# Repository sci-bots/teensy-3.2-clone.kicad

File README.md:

# Teensy 3.2 reference board clone

Teensy 3.2 reference board recreated in KiCad. This is based on a conversion of the original [eagle project](https://github.com/thewknd/teensy-boards) by [thewknd](https://github.com/thewknd).

Shared basket at mouser: http://www.mouser.com/ProjectManager/ProjectDetail.aspx?AccessID=719df5721e

Pre-programmed Bootloader Chip for DIY Teensy LC & 3.2 Projects: http://pjrc.com/store/ic_mkl02.html (IC_MKL04Z32_TQFP32)

Shared project on osh park: https://www.oshpark.com/shared_projects/h2HB6bQQ

### What is different from the "original" Teensy 3.2 DIY Reference Board

PJRC Teensy 3.2 DIY Reference Board https://www.oshpark.com/shared_projects/d3J03Zeb

- the silkscreen is a bit messed up  
  
- the actuator from the tactile switch is shorter (ALPS SKHHPKA010)

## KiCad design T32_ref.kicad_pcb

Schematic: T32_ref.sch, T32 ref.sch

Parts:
C1, C4, C5, C7, C8, C9, C12: 0.1uF; C_0603; Mfg_Part_No GRM155R71A104KA01D
C2, C3, C6: 2.2uF; C_0805; Mfg_Part_No TMK212B7225KG-TR
C10, C11: 22pF; C_0603; Mfg_Part_No VJ0603A220JXACW1BC
G1: 16MHz; HC49US; Mfg_Part_No ABL-16.000MHz-B1U
G2: 32.768kHz; TC26H; Mfg_Part_No CFS206-32.768KDZF-UB
K1: MK20DX256VLH7; LQFP64-05; Mfg_Part_No MK20DX256VLH7
K2: MKL04Z32VLC4; LQFP32-08
P1: LED_0805; Mfg_Part_No SML-211DTT86
R1: FUSE; R_0805; Mfg_Part_No 0ZCK0050FF2E
R2, R4: R_0603; Mfg_Part_No BLM18AG601SN1D
R3, R8: 470R; R_0603; Mfg_Part_No CRCW0603470RFKEA
R5, R6: 33R; R_0603; Mfg_Part_No ERJ-PA3F33R0V
R7: SOT-23; Mfg_Part_No BAT54C,215
S1: ALPS_SKHH; Mfg_Part_No SKHHPKA010
SJ1: SOLDERJUMPER
SX1, SX2, SX3, SX4, SX5, SX6, SX7, SX8, SX9, SX10, SX11, SX12, SX13, SX14, SX15, SX16, SX17, SX18, SX19, SX20, SX21, SX22, SX23, SX24, SX25, SX26, SX27, SX28, SX29, SX30, SX31, SX32, SX33, SX34, SX35, SX36, SX37, SX38, SX39, SX40, SX41, SX42, SX43, SX44, SX45, SX46, SX47, SX48, SX49, SX50, SX51, SX52, SX53, SX54, SX55, SX56, SX57, SX58, SX59, SX60: PIN; PTH_39MIL
T1: MCP1825S; SOT-223; Mfg_Part_No MCP1825S-3302E/DB
X1: MINI-USB; MOLEX_SD-67503-010; Mfg_Part_No 67503-1020

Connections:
/N$1: K2.7 (PTA3), SX59.1
/N$2: K1.22 (PTA0), K2.16 (PTB0), SX58.1
/N$3: K1.24 (PTA2), K2.17 (PTB1)
/N$5: C10.1, G1.1, K1.32 (PTA18)
/N$6: C11.1, G1.2, K1.33 (PTA19)
/N$7: G2.2 (1), K1.19 (XTAL32)
/N$8: G2.1 (2), K1.20 (EXTAL32)
/N$9: K2.18 (PTB2), S1.1, S1.2 (1), SX40.1
/N$10: K1.5 (USB0_DP), R6.2
/N$11: C8.1, K1.17 (VREF_OUT)
/N$12: K1.34 (RESET_B), K2.8 (PTA4), K2.25 (PTB5), SX38.1, SX56.1
/N$13: C7.1, K1.14 (VREFH), R3.2, SX16.1
/N$14: K1.6 (USB0_DM), R5.2
/N$15: C6.1, K1.13 (VDDA), R2.1, R3.1
/N$16: R6.1, X1.3
/N$17: R5.1, X1.2
/N$18: C3.1, R1.1, X1.1
/N$19: K1.23 (PTA1), K2.10 (PTA6), X1.4
/N$21: K1.45 (PTC2), SX5.1
/N$22: K1.44 (PTC1), SX6.1
/N$23: K1.63 (PTD6), SX7.1
/N$24: K1.62 (PTD5), SX8.1
/N$25: K1.37 (PTB2), SX9.1
/N$26: K1.38 (PTB3), SX10.1
/N$27: K1.36 (PTB1), SX11.1
/N$28: K1.35 (PTB0), SX13.1
/N$29: K1.43 (PTC0), SX15.1
/N$30: K1.58 (PTD1), SX17.1
/N$31: K1.50 (PTC5), P1.2, P1.+, SX18.1
/N$32: K1.52 (PTC7), SX19.1
/N$33: K1.51 (PTC6), SX20.1
/N$34: K1.49 (PTC4), SX21.1
/N$35: K1.46 (PTC3), SX22.1
/N$36: K1.60 (PTD3), SX23.1
/N$37: K1.59 (PTD2), SX24.1
/N$38: K1.61 (PTD4), SX25.1
/N$39: K1.64 (PTD7), SX26.1
/N$40: K1.29 (PTA13), SX27.1
/N$41: K1.28 (PTA12), SX28.1
/N$42: K1.57 (PTD0), SX29.1
/N$43: K1.40 (PTB17), SX30.1
/N$44: K1.39 (PTB16), SX31.1
/N$45: K1.12 (ADC0_DM3), SX33.1
/N$46: K1.26 (PTA4), SX35.1
/N$47: K1.41 (PTB18), SX36.1
/N$48: K1.1 (PTE0), SX37.1
/N$49: K1.56 (PTC11), SX39.1
/N$50: K1.55 (PTC10), SX41.1
/N$51: K1.53 (PTC8), SX43.1
/N$52: P1.1, P1.-, R8.2
/N$53: C6.2, C7.2, C8.2, K1.15 (VREFL), K1.16 (VSSA), R4.2, SX3.1
/N$54: K1.18 (DAC0), SX52.1
/N$55: K1.11 (ADC0_DP3), SX51.1
/N$57: K1.27 (PTA5), SX49.1
/N$58: K1.42 (PTB19), SX48.1
/N$59: K1.2 (PTE1), SX47.1
/N$60: K1.54 (PTC9), SX45.1
/N$61: C1.1, SJ1.2, SX2.1, T1.1 (IN)
/N$63: R7.2, SX46.1
/N$64: K1.10 (ADC0_DM0), SX12.1
/N$65: K1.9 (ADC0_DP0), SX14.1
/N$67: R1.2, SJ1.1, SX1.1
/N$68: C9.1, K1.21 (VBAT), R7.3
/N$69: C2.1, C4.1, C5.1, C12.1, K1.3 (VDD), K1.7 (VOUT33), K1.30 (VDD), K1.48 (VDD), K2.3 (VDD), K2.4 (VREFH), R2.2, R7.1, SX4.1, SX34.1, SX44.1, SX54.1, T1.3 (OUT)
/N$70: K1.25 (PTA3), K2.15 (PTA7), SX57.1
GND: C1.2, C2.2, C3.2, C4.2, C5.2, C9.2, C10.2, C11.2, C12.2, K1.4 (VSS), K1.31 (VSS), K1.47 (VSS), K2.5 (VREFL), K2.6 (VSS), R4.1, R8.1, S1.3, S1.4 (3), SX32.1, SX42.1, SX50.1, SX53.1, SX55.1, SX60.1, T1.2 (GND), T1.4, T1.PAD, X1.5, X1.P$1 (CASE), X1.P$2 (CASE), X1.P$3 (CASE), X1.P$4 (CASE), X1.P$5 (CASE), X1.P$6 (CASE)

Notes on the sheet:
VIN
AGND
3.3V
23 / A9
22 / A8
21 / A7
20 / A6
19 / A5
18 / A4
17 / A3
16 / A2
15 / A1
14 / A0
13 (LED)
GND
A13
A12
DAC / A14
VBAT
RESET
PROG
A11
A10
AREF
VUSB
SWD
SWC
EN'

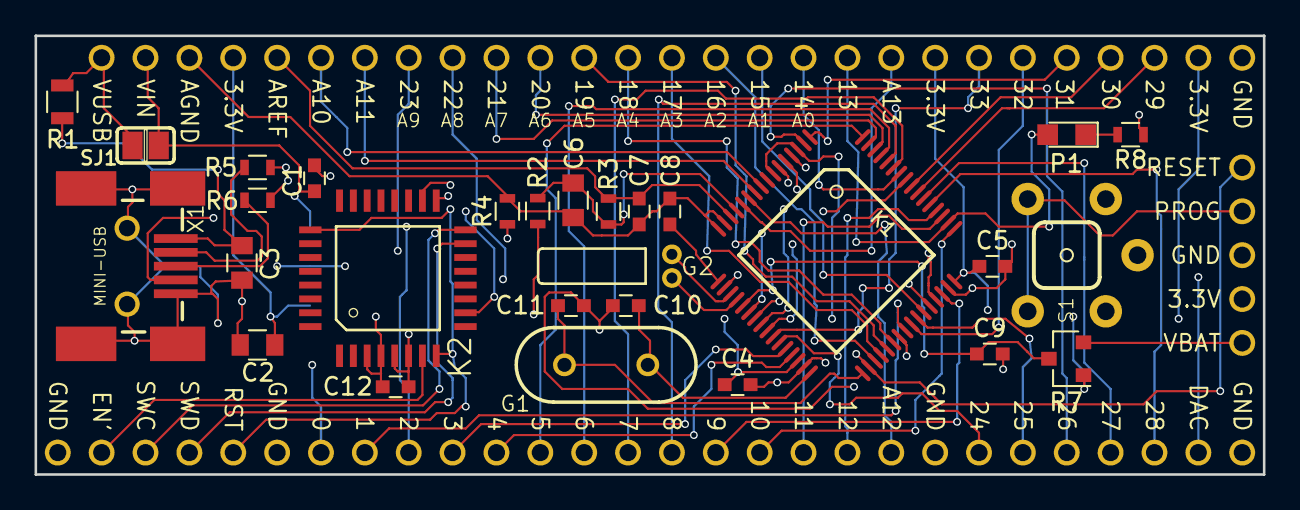
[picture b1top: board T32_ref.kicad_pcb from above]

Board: 4 copper layers, 71.1 x 25.4 mm, 89 parts (0 on the bottom side), 66 nets.

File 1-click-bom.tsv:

References,Qty,Description,Part Number,Digi-Key,Mouser,Newark
"C1, C4, C5, C7, C8, C9, C12",7,0.1uF,GRM155R71A104KA01D,490-6321-1-ND,GRM155R71A104KA01D,14T3278
"C2, C3, C6",3,2.2uF,TMK212B7225KG-TR,587-2991-1-ND,TMK212B7225KG-TR,92T9715
"C10, C11",2,22pF,VJ0603A220JXACW1BC,BC1229TR-ND,VJ0603A220JXACW1BC,57J8941
G1,1,16MHz,ABL-16.000MHZ-B1U,,ABL-16.000MHZ-B1U,
G2,1,32.768kHz,CFS206-32.768-KDZF-UB,,CFS206-32.768-KDZF-UB,
K1,1,MK20DX256VLH7,MK20DX256VLH7,MK20DX256VLH7-ND,MK20DX256VLH7,24W6507
P1,1,~,SML-211DTT86,511-1291-1-ND,SML-211DTT86,
R1,1,FUSE,0ZCK0050FF2E,507-1813-1-ND,0ZCK0050FF2E,
"R2, R4",2,~,BLM18AG601SN1D,490-1014-1-ND,BLM18AG601SN1D,73M9057
"R3, R8",2,470R,CRCW0603470RFKEA,541-470HCT-ND,CRCW0603470RFKEA,52K8556
"R5, R6",2,33R,ERJ-PA3F33R0V,P33.00BYCT-ND,ERJ-PA3F33R0V,84X4678
R7,1,~,"BAT54C,215",1727-2902-1-ND,"BAT54C,215",75R4975
S1,1,~,SKHHPKA010,,SKHHPKA010,
T1,1,MCP1825S,MCP1825S-3302E/DB,MCP1825S-3302E/DB-ND,MCP1825S-3302E/DB,26M9961
X1,1,MINI-USB,675031020,WM5461CT-ND,,

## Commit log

2017-03-10 KiCad conversion of thewknd's reference design
    https://github.com/thewknd/teensy-boards/tree/master/Teensy%203.2%20reference%20board%20clone
2017-03-15 Convert to new library format and fix DRC errors
2017-03-15 Replace common footprints with KiCad versions
2017-03-15 Remove unnecessary files
2017-03-15 Add part numbers to schematic and export BOM
2017-03-15 Remove space from paths
2017-03-15 Add gerber, svg, png and pdf outputs
2017-03-30 Add 1-click-bom.tsv for kitnic.it test
2018-03-26 Make compatible with kitspace.org
2019-10-24 Fix cap footprint
    Fixes #2
2019-10-24 Change kitspace color to black
2019-10-24 Rename front and bottom copper gerber layers
    What's that gerber couldn't deal with the names you chose yet. Switching
    to the KiCad defaults.
    https://github.com/tracespace/tracespace/tree/master/packages/whats-that-gerber
2019-10-24 Remove SX* pin holes from BOM
2019-10-25 Update kicad_pcb and pro to use new layer names
